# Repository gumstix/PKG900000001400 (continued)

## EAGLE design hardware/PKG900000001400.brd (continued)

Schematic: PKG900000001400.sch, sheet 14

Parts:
C5, C15, C105, C106, C108: 0.1uF; 0201
C107, C109: 0.01uF; 0201
L2, L3, L4, L9: DLP11SN900HL2; 0504-DLP11S
R38: 75R; 0402
RP3: DNP; 741X08
U3: HDMI; 47151-001
U8: TPD13S523TSSOP; TSSOP16
U$29: TXS0104E; S-PVQFN-N14

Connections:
2.5.0V_VCC_5.0: C5.1, C108.1, U8.5 (5V_SUPPLY), U$29.14 (VCCB); also elsewhere on the board
19.HDMI0_CEC: RP3.4, U$29.2 (A1); also elsewhere on the board
19.HDMI0_CLOCK_N: L4.2, U8.9 (D3-); also elsewhere on the board
19.HDMI0_CLOCK_P: L4.3, U8.10 (D3+); also elsewhere on the board
19.HDMI0_D0_N: L3.2, U8.11 (D2-); also elsewhere on the board
19.HDMI0_D0_P: L3.3, U8.12 (D2+); also elsewhere on the board
19.HDMI0_D1_N: L2.2, U8.13 (D1-); also elsewhere on the board
19.HDMI0_D1_P: L2.3, U8.14 (D1+); also elsewhere on the board
19.HDMI0_D2_N: L9.2, U8.15 (D0-); also elsewhere on the board
19.HDMI0_D2_P: L9.3, U8.16 (D0+); also elsewhere on the board
19.HDMI0_DDC_SCL: RP3.3, U$29.3 (A2); also elsewhere on the board
19.HDMI0_DDC_SDA: RP3.2, U$29.4 (A3); also elsewhere on the board
19.HDMI0_HPD: RP3.1, U$29.5 (A4); also elsewhere on the board
19.VLOGIC_VLOGIC: C15.1, C106.1, C107.1, C109.1, U$29.1 (VCCA), U$29.8 (OE); also elsewhere on the board
CEC$17: RP3.5, U3.13, U8.1 (CTRL1), U$29.13 (B1)
COMMON_SHIELD: U3.G1 (20), U3.G2 (21), U3.G3 (22), U3.G4 (23); also elsewhere on the board
CON_5V0$17: C105.1, U3.18, U8.6 (5V_OUT)
DDC_SCL$17: RP3.6, U3.15, U8.2 (CTRL2), U$29.12 (B2)
DDC_SDA$17: RP3.7, U3.16, U8.3 (CTRL3), U$29.11 (B3)
GND: C5.2, C15.2, C105.2, C106.2, C107.2, C108.2, C109.2, R38.1, U3.2, U3.5, U3.8, U3.11, U3.17, U8.8 (GND), U$29.7 (GND); also elsewhere on the board
HPD$17: RP3.8, U3.19, U8.4 (CTRL4), U$29.10 (B4)
TXD0_CONN_N$17: L3.1, U3.9
TXD0_CONN_P$17: L3.4, U3.7
TXD1_CONN_N$17: L2.1, U3.6
TXD1_CONN_P$17: L2.4, U3.4
TXD2_CONN_N$17: L9.1, U3.3
TXD2_CONN_P$17: L9.4, U3.1
TXDC_CONN_N$17: L4.1, U3.12
TXDC_CONN_P$17: L4.4, U3.10
UTIL$17: R38.2, U3.14, U8.7 (CTRL5)

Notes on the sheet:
HDMI
PWR<->GND via stitching around bottom side signals (per Toradex layout guidelines)
TPD13S523 sheet says to GND unused pins with 75ohm resistor.

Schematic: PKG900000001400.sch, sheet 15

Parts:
C110: 0.1uF; 0201
R13, R44: 10K 1%; 0201
RP1, RP2: DNP; RP741X083
U2: TS3A5223; UQFN-10

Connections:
1.USB_DEVICE_VBUS: R13.2; also elsewhere on the board
18.UART1_RXD: RP1.1, U2.7 (NC2); also elsewhere on the board
18.UART1_TXD: RP1.2, U2.5 (NC1); also elsewhere on the board
18.UART2_RXD: RP2.4, U2.10 (NO2); also elsewhere on the board
18.UART2_TXD: RP2.3, U2.2 (NO1); also elsewhere on the board
19.UART0_RXD: RP1.8, RP2.5, U2.9 (COM2); also elsewhere on the board
19.UART0_TXD: RP1.7, RP2.6, U2.3 (COM1); also elsewhere on the board
19.VLOGIC_VLOGIC: C110.1, U2.1 (VCC); also elsewhere on the board
GND: C110.2, R44.1, U2.6 (GND); also elsewhere on the board
UART_SEL$: R13.1, R44.2, U2.4 (SEL1), U2.8 (SEL2)

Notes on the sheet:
Quad 2 Input MUX

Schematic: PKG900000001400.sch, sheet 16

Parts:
J2, J7: DF40C-100DS-0.4V(51); HRS_DF40C-100DS-0.4V(51)
MP1, MP2, MP3, MP4: 9774015151R; WA-SMSI_9774___151
Q1: BSS138; SOT23
Q2, Q3: FDN360P; SOT23
R1, R3: 0R; 0201
R2: DNP; 0201
R5: 10K 1%; 0201

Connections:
1.8V_OUT$19: J7.88, J7.90, R2.1
2.5.0V_VCC_5.0: J7.77, J7.79, J7.81, J7.83, J7.85, J7.87; also elsewhere on the board
3.3V_OUT$19: J7.84, J7.86, Q2.3 (D), R1.1
19.3.3V_VCC_3.3: Q3.3 (D), R3.2
19.1000BASET_LINK_100: J7.19
19.1000BASET_LINK_1000: J7.17; also elsewhere on the board
19.1000BASET_LINK_ACT: J7.15; also elsewhere on the board
19.1000BASET_TR0_N: J7.10; also elsewhere on the board
19.1000BASET_TR0_P: J7.12; also elsewhere on the board
19.1000BASET_TR1_N: J7.6; also elsewhere on the board
19.1000BASET_TR1_P: J7.4; also elsewhere on the board
19.1000BASET_TR2_N: J7.9; also elsewhere on the board
19.1000BASET_TR2_P: J7.11; also elsewhere on the board
19.1000BASET_TR3_N: J7.5; also elsewhere on the board
19.1000BASET_TR3_P: J7.3; also elsewhere on the board
19.CAM0_C_N: J2.40; also elsewhere on the board
19.CAM0_C_P: J2.42; also elsewhere on the board
19.CAM0_D1_N: J2.28; also elsewhere on the board
19.CAM0_D1_P: J2.30; also elsewhere on the board
19.CAM0_D2_N: J2.34; also elsewhere on the board
19.CAM0_D2_P: J2.36; also elsewhere on the board
19.CAM1_C_N: J2.27; also elsewhere on the board
19.CAM1_C_P: J2.29; also elsewhere on the board
19.CAM1_D1_N: J2.15; also elsewhere on the board
19.CAM1_D1_P: J2.17; also elsewhere on the board
19.CAM1_D2_N: J2.21; also elsewhere on the board
19.CAM1_D2_P: J2.23; also elsewhere on the board
19.CAM1_D3_N: J2.33
19.CAM1_D3_P: J2.35
19.CAM1_D4_N: J2.39
19.CAM1_D4_P: J2.41
19.DSI1_C_N: J2.87; also elsewhere on the board
19.DSI1_C_P: J2.89; also elsewhere on the board
19.DSI1_D1_N: J2.75; also elsewhere on the board
19.DSI1_D1_P: J2.77; also elsewhere on the board
19.DSI1_D2_N: J2.81; also elsewhere on the board
19.DSI1_D2_P: J2.83; also elsewhere on the board
19.DSI1_D3_N: J2.93
19.DSI1_D3_P: J2.95
19.DSI1_D4_N: J2.94
19.DSI1_D4_P: J2.96
19.GPIO2_GPIO: J7.58; also elsewhere on the board
19.GPIO3_GPIO: J7.56; also elsewhere on the board
19.GPIO4_GPIO: J7.54; also elsewhere on the board
19.GPIO5_GPIO: J7.34; also elsewhere on the board
19.GPIO6_GPIO: J7.30; also elsewhere on the board
19.GPIO7_GPIO: J7.37; also elsewhere on the board
19.GPIO8_GPIO: J7.39; also elsewhere on the board
19.GPIO9_GPIO: J7.40; also elsewhere on the board
19.GPIO10_GPIO: J7.44; also elsewhere on the board
19.GPIO11_GPIO: J7.38; also elsewhere on the board
19.GPIO12_GPIO: J7.31; also elsewhere on the board
19.GPIO13_GPIO: J7.28; also elsewhere on the board
19.GPIO16_GPIO: J7.29; also elsewhere on the board
19.GPIO17_GPIO: J7.50; also elsewhere on the board
19.GPIO18_GPIO: J7.49; also elsewhere on the board
19.GPIO19_GPIO: J7.26; also elsewhere on the board
19.GPIO20_GPIO: J7.27; also elsewhere on the board
19.GPIO21_GPIO: J7.25; also elsewhere on the board
19.GPIO22_GPIO: J7.46; also elsewhere on the board
19.GPIO23_GPIO: J7.47; also elsewhere on the board
19.GPIO24_GPIO: J7.45; also elsewhere on the board
19.GPIO25_GPIO: J7.41; also elsewhere on the board
19.GPIO26_GPIO: J7.24; also elsewhere on the board
19.GPIO27_GPIO: J7.48; also elsewhere on the board
19.GPIO_CAMERA_GPIO: J7.97; also elsewhere on the board
19.HDMI0_CEC: J2.51; also elsewhere on the board
19.HDMI0_CLOCK_N: J2.90; also elsewhere on the board
19.HDMI0_CLOCK_P: J2.88; also elsewhere on the board
19.HDMI0_D0_N: J2.84; also elsewhere on the board
19.HDMI0_D0_P: J2.82; also elsewhere on the board
19.HDMI0_D1_N: J2.78; also elsewhere on the board
19.HDMI0_D1_P: J2.76; also elsewhere on the board
19.HDMI0_D2_N: J2.72; also elsewhere on the board
19.HDMI0_D2_P: J2.70; also elsewhere on the board
19.HDMI0_DDC_SCL: J2.100; also elsewhere on the board
19.HDMI0_DDC_SDA: J2.99; also elsewhere on the board
19.HDMI0_HPD: J2.53; also elsewhere on the board
19.I2C_ID_SCL: J7.35; also elsewhere on the board
19.I2C_ID_SDA: J7.36; also elsewhere on the board
19.I2C_SCL: J7.80; also elsewhere on the board
19.I2C_SDA: J7.82; also elsewhere on the board
19.NRESET_NRESET: J7.92; also elsewhere on the board
19.PCIE_CLKREQ_GPIO: J2.2; also elsewhere on the board
19.PCIE_CLK_N: J2.12; also elsewhere on the board
19.PCIE_CLK_P: J2.10; also elsewhere on the board
19.PCIE_RST_GPIO: J2.9; also elsewhere on the board
19.PCIE_RX0_N: J2.18; also elsewhere on the board
19.PCIE_RX0_P: J2.16; also elsewhere on the board
19.PCIE_TX0_N: J2.24; also elsewhere on the board
19.PCIE_TX0_P: J2.22; also elsewhere on the board
19.SYS_EN_SYSEN: J7.100, Q1.1 (G), R5.2; also elsewhere on the board
19.UART0_RXD: J7.51; also elsewhere on the board
19.UART0_TXD: J7.55; also elsewhere on the board
19.USB3_CC1_GPIO: J7.94
19.USB3_CC2_GPIO: J7.96
19.USB_HOST_D_N: J2.3; also elsewhere on the board
19.USB_HOST_D_P: J2.5; also elsewhere on the board
19.VLOGIC_VLOGIC: R3.1; also elsewhere on the board
!RPIBOOT$19: J7.93; also elsewhere on the board
DS_LOAD$19: Q2.2 (S), Q3.2 (S)
EEPROM_!WP: J7.20
ETH_SYNC_IN: J7.16
ETH_SYNC_OUT: J7.18
GLOBAL_EN: J7.99
GND: J2.7, J2.8, J2.13, J2.14, J2.19, J2.20, J2.25, J2.26, J2.31, J2.32, J2.37, J2.38, J2.44, J2.50, J2.55, J2.56, J2.61, J2.62, J2.67, J2.68, J2.73, J2.74, J2.79, J2.80, J2.85, J2.86, J2.91, J2.92, J2.97, J2.98, J7.1, J7.2, J7.7, J7.8, J7.13, J7.14, J7.22, J7.23, J7.32, J7.33, J7.42, J7.43, J7.52, J7.53, J7.59, J7.60, J7.65, J7.66, J7.71, J7.74, J7.98, MP1.1, MP2.1, MP3.1, MP4.1, Q1.2 (S), R5.1; also elsewhere on the board
GPIO_VREF$19: J7.78, R1.2, R2.2; also elsewhere on the board
LOAD_GATE$19: Q1.3 (D), Q2.1 (G), Q3.1 (G)
PI_!LED_ACT: J7.21
PI_LED_!PWR: J7.95
SD_PWR_ON: J7.75
SD_VDD_OV: J7.73
VDAC_COMP: J2.11

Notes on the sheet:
Raspberry Pi CM4
GPIO
High Speed

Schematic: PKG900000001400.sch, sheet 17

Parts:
C6: 0.1uF; 0201
IC6: CAT24C256YI-G; TSSOP8
R6, R7, R8: 100K 1%; 0201
R9, R10: 1K5; 0201
R11: 10K 1%; 0201
S1: EVQ; KMT0

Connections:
19.I2C_ID_SCL: IC6.6 (SCL), R10.1; also elsewhere on the board
19.I2C_ID_SDA: IC6.5 (SDA), R9.1; also elsewhere on the board
!RPIBOOT$19: S1.3 (B), S1.4 (B'); also elsewhere on the board
A0$19: IC6.1 (A0), R8.2
A1$19: IC6.2 (A1), R7.2
A2$19: IC6.3 (A2), R6.2
GND: C6.2, IC6.4 (GND), IC6.7 (WP), R6.1, R7.1, R11.1; also elsewhere on the board
GPIO_VREF$19: C6.1, IC6.8 (VCC), R8.1, R9.2, R10.2; also elsewhere on the board
RPIBOOT_SWITCH$19: R11.2, S1.1 (A), S1.2 (A')

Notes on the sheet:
Raspberry Pi CM4

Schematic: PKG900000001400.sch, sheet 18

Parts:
C2: 220uF/6.3V; 1206
C3: DNP; 1206
C4: 0.1uF; 0201
D1, D2: PS04LTVA1; D0402
D3, D4: B72590D50A060; D0402
FB1, FB2: 120R 1A; 0402
IC1: TPS2051; MSOP8-PAD
J8: USB-A-S
L1: DLP11SN900HL2; 0504-DLP11S

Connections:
2.5.0V_VCC_5.0: C4.1, IC1.2 (IN), IC1.3 (IN); also elsewhere on the board
3.3.3V_VCC_3.3: IC1.4 (EN); also elsewhere on the board
21.USB1_D_N: L1.2; also elsewhere on the board
21.USB1_D_P: L1.3; also elsewhere on the board
21.USB1_NOC: IC1.5 (NOC)
21.USB1_VBUS: FB1.1, IC1.6 (OUT), IC1.7 (OUT), IC1.8 (OUT)
COMMON_SHIELD: D1.P1, D2.P1, D3.P1, D4.P1, J8.P$5 (P1), J8.P$6 (P2); also elsewhere on the board
GND: C2.2, C3.2, C4.2, FB2.1, IC1.1 (GND), IC1.TP (GND); also elsewhere on the board
USBH_GND$20: D3.P2, FB2.2, J8.GND
USBH_N$20: D2.P2, J8.D-, L1.1
USBH_P$20: D1.P2, J8.D+ (VBUS), L1.4
USBH_VBUSF$20: C2.1, C3.1, D4.P2, FB1.2, J8.VBUS (D+)

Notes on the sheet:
USB HOST

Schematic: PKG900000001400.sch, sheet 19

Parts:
C103: 0.1uF; 0201
R27, R28: 10K 1%; 0201
U26: TS3USB30; UQFN-10

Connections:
3.3.3V_VCC_3.3: C103.1, U26.9 (VCC); also elsewhere on the board
19.USB_HOST_D_N: U26.5 (D-); also elsewhere on the board
19.USB_HOST_D_P: U26.3 (D+); also elsewhere on the board
21.USB1_D_N: U26.7 (D1-); also elsewhere on the board
21.USB1_D_P: U26.1 (D1+); also elsewhere on the board
21.USB2_D_N: U26.6 (D2-); also elsewhere on the board
21.USB2_D_P: U26.2 (D2+); also elsewhere on the board
21.USB2_VBUS: R27.2, U26.10 (S); also elsewhere on the board
GND: C103.2, R27.1, R28.1, U26.4 (GND); also elsewhere on the board
USBMUX_OE$13: R28.2, U26.8 (!OE)

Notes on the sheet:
USB 2-Port Switch

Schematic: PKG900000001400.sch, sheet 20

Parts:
U4: MALE; 2X20

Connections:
2.5.0V_VCC_5.0: U4.2, U4.4; also elsewhere on the board
3.3.3V_VCC_3.3: U4.1, U4.17; also elsewhere on the board
18.UART1_RXD: U4.10; also elsewhere on the board
18.UART1_TXD: U4.8; also elsewhere on the board
19.GPIO2_GPIO: U4.3; also elsewhere on the board
19.GPIO3_GPIO: U4.5; also elsewhere on the board
19.GPIO4_GPIO: U4.7; also elsewhere on the board
19.GPIO5_GPIO: U4.29; also elsewhere on the board
19.GPIO6_GPIO: U4.31; also elsewhere on the board
19.GPIO7_GPIO: U4.26; also elsewhere on the board
19.GPIO8_GPIO: U4.24; also elsewhere on the board
19.GPIO9_GPIO: U4.21; also elsewhere on the board
19.GPIO10_GPIO: U4.19; also elsewhere on the board
19.GPIO11_GPIO: U4.23; also elsewhere on the board
19.GPIO12_GPIO: U4.32; also elsewhere on the board
19.GPIO13_GPIO: U4.33; also elsewhere on the board
19.GPIO16_GPIO: U4.36; also elsewhere on the board
19.GPIO17_GPIO: U4.11; also elsewhere on the board
19.GPIO18_GPIO: U4.12; also elsewhere on the board
19.GPIO19_GPIO: U4.35; also elsewhere on the board
19.GPIO20_GPIO: U4.38; also elsewhere on the board
19.GPIO21_GPIO: U4.40; also elsewhere on the board
19.GPIO22_GPIO: U4.15; also elsewhere on the board
19.GPIO23_GPIO: U4.16; also elsewhere on the board
19.GPIO24_GPIO: U4.18; also elsewhere on the board
19.GPIO25_GPIO: U4.22; also elsewhere on the board
19.GPIO26_GPIO: U4.37; also elsewhere on the board
19.GPIO27_GPIO: U4.13; also elsewhere on the board
GND: U4.6, U4.9, U4.14, U4.20, U4.25, U4.30, U4.34, U4.39; also elsewhere on the board
P27: U4.27
P28: U4.28

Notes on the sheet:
40-Pin Header

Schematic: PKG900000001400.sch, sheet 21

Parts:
J9: FPC-15VERT; 1-1734248-5

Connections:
3.3.3V_VCC_3.3: J9.1_15 (15); also elsewhere on the board
19.CAM1_C_N: J9.1_8 (8); also elsewhere on the board
19.CAM1_C_P: J9.1_9 (9); also elsewhere on the board
19.CAM1_D1_N: J9.1_2 (2); also elsewhere on the board
19.CAM1_D1_P: J9.1_3 (3); also elsewhere on the board
19.CAM1_D2_N: J9.1_5 (5); also elsewhere on the board
19.CAM1_D2_P: J9.1_6 (6); also elsewhere on the board
19.GPIO_CAMERA_GPIO: J9.1_11 (11); also elsewhere on the board
19.I2C_SCL: J9.1_13 (13); also elsewhere on the board
19.I2C_SDA: J9.1_14 (14); also elsewhere on the board
GND: J9.1_1 (1), J9.1_4 (4), J9.1_7 (7), J9.1_10 (10); also elsewhere on the board

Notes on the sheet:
RPi CSI Vertical Connector

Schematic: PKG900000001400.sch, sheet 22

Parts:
J10: FPC-15VERT; 1-1734248-5

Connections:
3.3.3V_VCC_3.3: J10.1_15 (15); also elsewhere on the board
19.CAM0_C_N: J10.1_8 (8); also elsewhere on the board
19.CAM0_C_P: J10.1_9 (9); also elsewhere on the board
19.CAM0_D1_N: J10.1_2 (2); also elsewhere on the board
19.CAM0_D1_P: J10.1_3 (3); also elsewhere on the board
19.CAM0_D2_N: J10.1_5 (5); also elsewhere on the board
19.CAM0_D2_P: J10.1_6 (6); also elsewhere on the board
19.GPIO_CAMERA_GPIO: J10.1_11 (11); also elsewhere on the board
19.I2C_ID_SCL: J10.1_13 (13); also elsewhere on the board
19.I2C_ID_SDA: J10.1_14 (14); also elsewhere on the board
GND: J10.1_1 (1), J10.1_4 (4), J10.1_7 (7), J10.1_10 (10); also elsewhere on the board

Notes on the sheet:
RPi CSI Vertical Connector

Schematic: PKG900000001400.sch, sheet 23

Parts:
J1: FPC-15VERT; 1-1734248-5

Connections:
3.3.3V_VCC_3.3: J1.1_14 (14), J1.1_15 (15); also elsewhere on the board
19.DSI1_C_N: J1.1_5 (5); also elsewhere on the board
19.DSI1_C_P: J1.1_6 (6); also elsewhere on the board
19.DSI1_D1_N: J1.1_8 (8); also elsewhere on the board
19.DSI1_D1_P: J1.1_9 (9); also elsewhere on the board
19.DSI1_D2_N: J1.1_2 (2); also elsewhere on the board
19.DSI1_D2_P: J1.1_3 (3); also elsewhere on the board
19.I2C_SCL: J1.1_11 (11); also elsewhere on the board
19.I2C_SDA: J1.1_12 (12); also elsewhere on the board
GND: J1.1_1 (1), J1.1_4 (4), J1.1_7 (7), J1.1_10 (10), J1.1_13 (13); also elsewhere on the board

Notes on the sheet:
DSI Vertical Connector

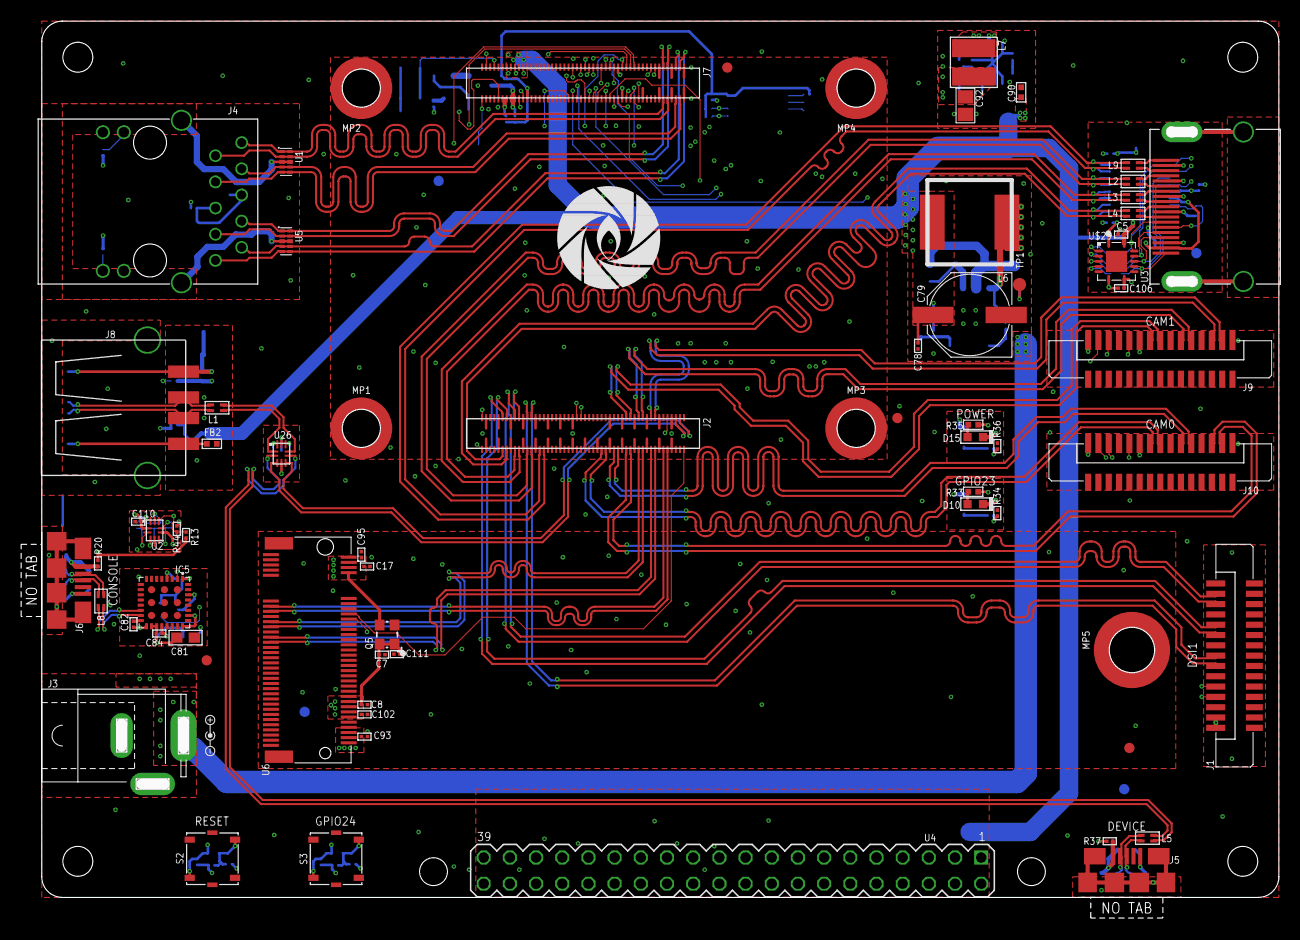
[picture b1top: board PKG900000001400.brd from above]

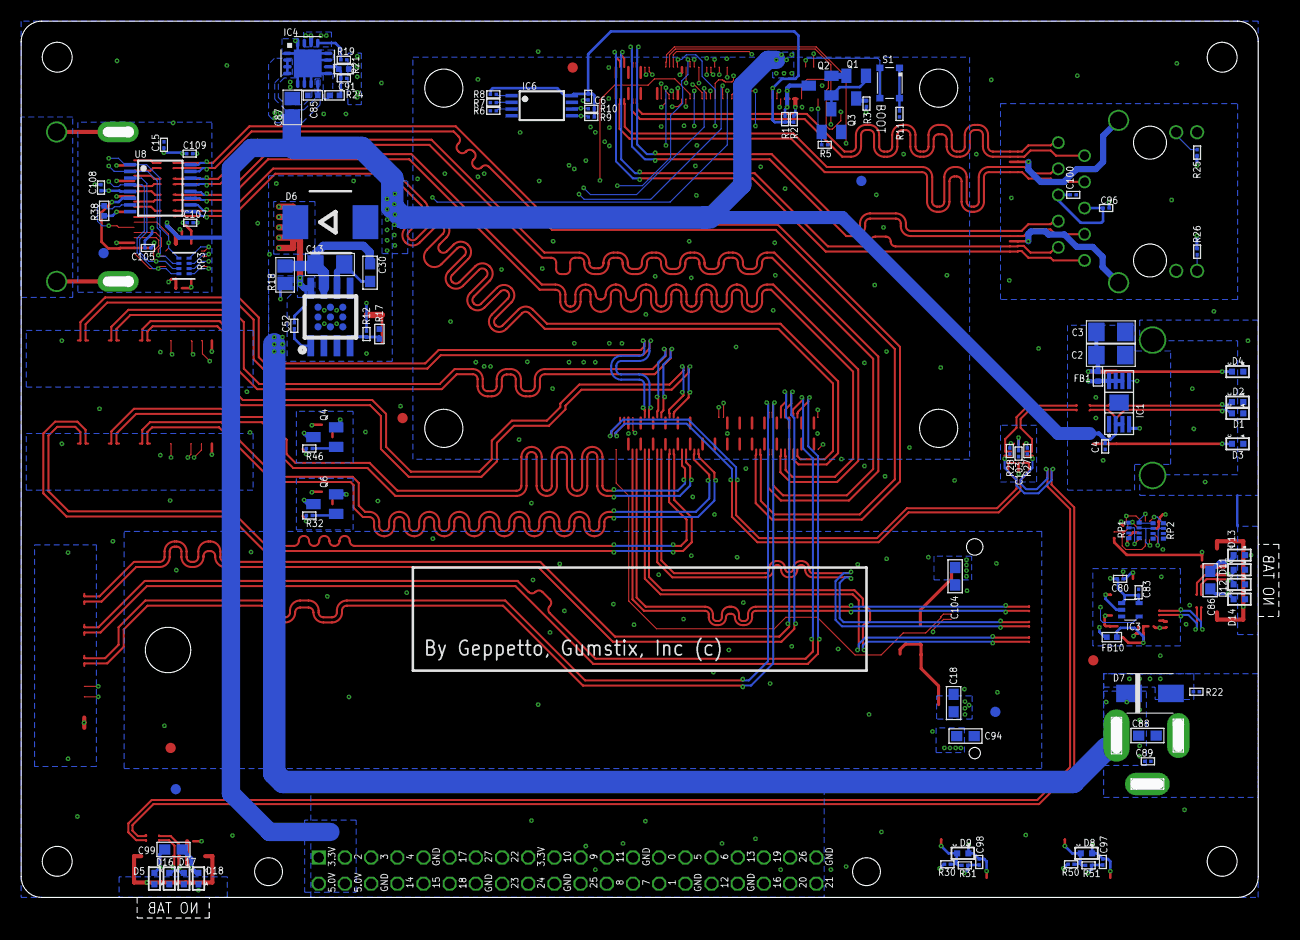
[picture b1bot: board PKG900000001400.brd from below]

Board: 6 copper layers, 122.0 x 87.0 mm, 170 parts (95 on the bottom side), 161 nets.

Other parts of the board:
U$14, U$16, U$18, U$20: DNP; GEPPETTO_HOLE_2.9

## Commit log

2020-10-13 Add README content, spec sheet, autodoc and folders
2020-10-15 Added hardware documents for revision 2.
2020-10-15 add links to sch and brd
2020-10-19 Update firmware image to Ubuntu 20.04 CM4 image.
2020-11-23 Update firmware.md
    Add image username and password information.
